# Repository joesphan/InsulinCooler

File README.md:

# Insulin Cooler

This repository is for my senior project

#### Problem Statement

There is a large population of diabetic citizens who require doses of insulin every day. Long-term portable methods of insulin storage are very expensive.

#### Methodology and Limitations

Insulin must be stored at temperatures from 36&deg;F to 46&deg;F. Using 3d printing to maximalize thermal insulation in the chassis, combined with peltier coolers, lithium-ion batteries and IOT ESP32, it should be reasonably feasible to create a cooler for under $50.

The specs I submitted for my coursework states that the cooler must have a battery life of at least 48 hours. However, I have made it a personal goal to maximize thermal efficiency to achieve two weeks or more.

Using 3d printing, I should be able to create an airgap insulation.

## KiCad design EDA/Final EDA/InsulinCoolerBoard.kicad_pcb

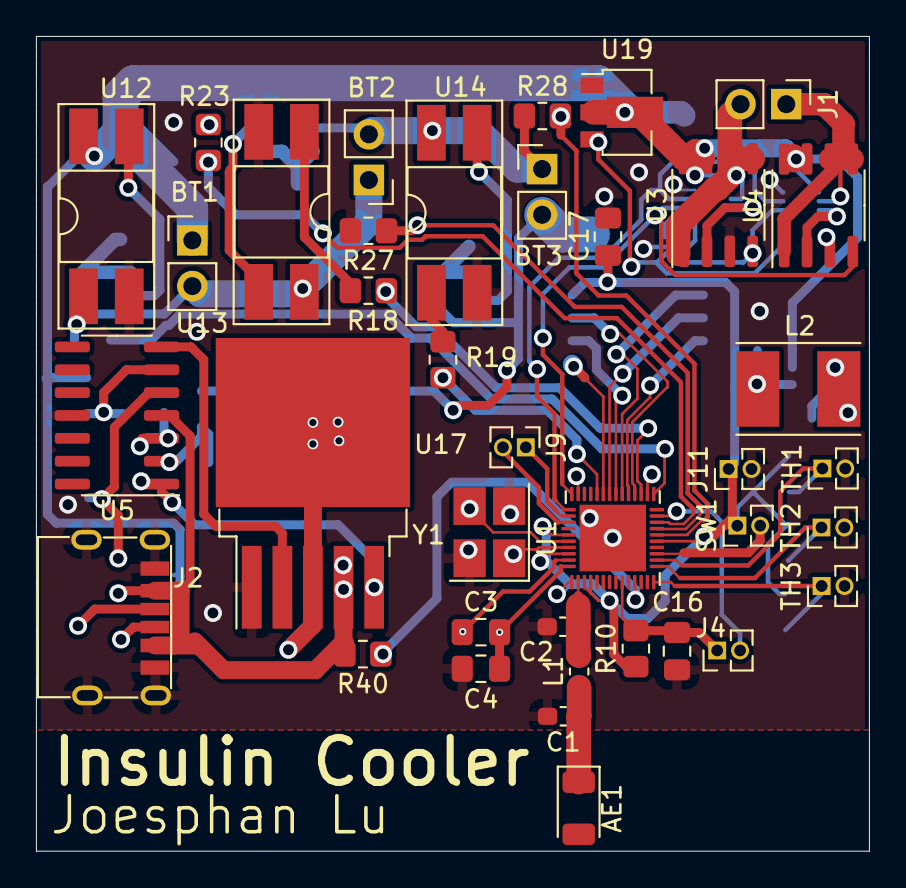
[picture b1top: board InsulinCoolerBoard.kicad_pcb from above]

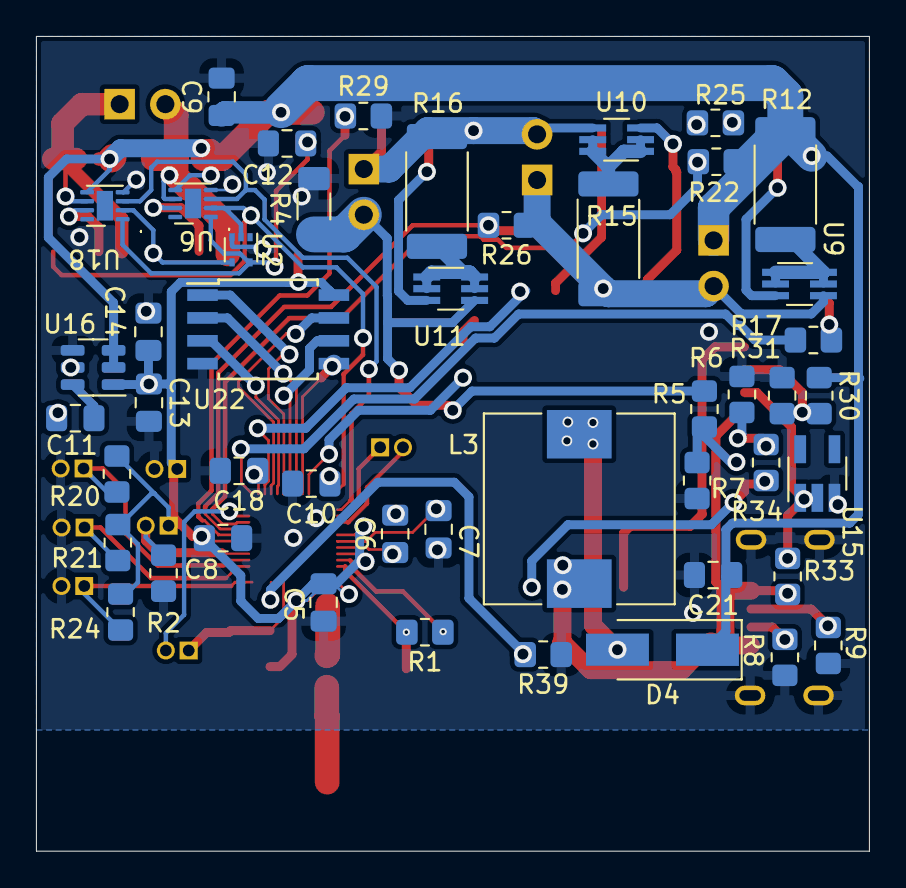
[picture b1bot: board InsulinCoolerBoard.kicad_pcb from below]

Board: 2 copper layers, 46.3 x 45.3 mm, 85 parts (47 on the bottom side), 65 nets.

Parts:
AE1: Antenna_Chip; Johanson_2450AT18x100
BT1, BT2, BT3: Battery_Cell; PinHeader_1x02_P2.54mm_Vertical
C1: 3.797pF; C_0603_1608Metric_Pad1.08x0.95mm_HandSolder
C2: 4.64pF; C_0603_1608Metric_Pad1.08x0.95mm_HandSolder
C3: 3.3nF; C_0805_2012Metric_Pad1.18x1.45mm_HandSolder
C4: 10nF; C_0805_2012Metric_Pad1.18x1.45mm_HandSolder
C5, C8, C10, C11, C16, C17, C21: 100nF; C_0805_2012Metric_Pad1.18x1.45mm_HandSolder
C6, C7: 10pF; C_0805_2012Metric_Pad1.18x1.45mm_HandSolder
C9, C12: 10uF; C_0805_2012Metric_Pad1.18x1.45mm_HandSolder
C13, C14: 22uF; C_0805_2012Metric_Pad1.18x1.45mm_HandSolder
C18: 1uF; C_0805_2012Metric_Pad1.18x1.45mm_HandSolder
D4: SS34; D_SMA_Handsoldering
J1: Peltier Connection; PinHeader_1x02_P2.54mm_Vertical
J2: USB_C_Receptacle_USB2.0; USB4125-GF-A
J4, J9, J11: PROG_PORT; PinHeader_1x02_P1.27mm_Vertical
L1: 1.807nH; L_0603_1608Metric_Pad1.05x0.95mm_HandSolder
L2: 3.3uH NRS5024T3R3NMGJ; L_Taiyo-Yuden_NR-50xx_HandSoldering
L3: 33uH; L_10.4x10.4_H4.8
R1, R10: 20k; R_0805_2012Metric_Pad1.20x1.40mm_HandSolder
R2: 10k; R_0805_2012Metric_Pad1.20x1.40mm_HandSolder
R4: .1; R_1206_3216Metric_Pad1.30x1.75mm_HandSolder
R5, R6: 1k; R_0805_2012Metric_Pad1.20x1.40mm_HandSolder
R7, R34: 12.5k; R_0805_2012Metric_Pad1.20x1.40mm_HandSolder
R8, R9: 5.1k; R_0805_2012Metric_Pad1.20x1.40mm_HandSolder
R12, R15, R16: 28.7; R_2512_6332Metric_Pad1.40x3.35mm_HandSolder
R17, R18, R19: 200; R_0805_2012Metric_Pad1.20x1.40mm_HandSolder
R20, R21, R24: 90k; R_0805_2012Metric_Pad1.20x1.40mm_HandSolder
R22, R26: 180k; R_0805_2012Metric_Pad1.20x1.40mm_HandSolder
R23: 36k; R_0805_2012Metric_Pad1.20x1.40mm_HandSolder
R25: 4.3k; R_0805_2012Metric_Pad1.20x1.40mm_HandSolder
R27: 68k; R_0805_2012Metric_Pad1.20x1.40mm_HandSolder
R28: 510k; R_0805_2012Metric_Pad1.20x1.40mm_HandSolder
R29: 620k; R_0805_2012Metric_Pad1.20x1.40mm_HandSolder
R30: 200k; R_0805_2012Metric_Pad1.20x1.40mm_HandSolder
R31: 51k; R_0805_2012Metric_Pad1.20x1.40mm_HandSolder
R33: 500; R_0805_2012Metric_Pad1.20x1.40mm_HandSolder
R39: 150k; R_0805_2012Metric_Pad1.20x1.40mm_HandSolder
R40: 100k; R_0805_2012Metric_Pad1.20x1.40mm_HandSolder
SW1: Power Switch; PinHeader_1x02_P1.27mm_Vertical
TH1, TH2, TH3: SDNT2012X103F3950FTF; PinHeader_1x02_P1.27mm_Vertical
U1: ESP32-D-WD-V3; QFN-48-1EP_5x5mm_P0.35mm_EP3.7x3.7mm
U2: NL17SZ14; SOT-553
U3, U4: DMT3020LSDQ; SO-8_3.9x4.9mm_P1.27mm
U5: LM324; SOIC-14_3.9x8.7mm_P1.27mm
U6, U18: slg55021; TDFN_8_2x2mm_EP_0.9x1.65mm
U9, U10, U11: BSD316; SOT-363_SC-70-6_Handsoldering
U12, U13, U14: PC817; DIP-4_W8.89mm_SMDSocket_LongPads
U15: AS431; SOT-23-5_HandSoldering
U16: AP63203WU; TSOT-23-6
U17: XL6009; TO-263-5_TabPin3
U19: HT75xx-1-SOT89; SOT-89-3
U22: W25Q40CL; SOIC-8W_5.3x5.3mm_P1.27mm
Y1: Crystal_GND24; Crystal_SMD_SeikoEpson_FA238-4Pin_3.2x2.5mm_HandSoldering

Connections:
+3V3: C5.1, C8.1, C13.1, C14.1, C17.1, J11.1, L2.2, R10.1, R20.1, R21.1, R24.1, SW1.1, U1.1 (VDDA), U1.3 (VDD3P3), U1.4 (VDD3P3), U1.19 (VDD3P3_RTC), U1.43 (VDDA), U1.46 (VDDA), U16.1 (FB), U22.8 (VCC)
+5V: C12.1, U2.5 (VCC), U6.1 (VCC), U18.1 (VCC), U19.3 (VOUT)
/MCU/CELL_DSCHG_1_MCU: R19.2, U1.34 (GPIO5)
/MCU/CELL_DSCHG_2_MCU: R18.2, U1.27 (GPIO17)
/MCU/CELL_DSCHG_3_MCU: R17.2, U1.25 (GPIO16)
/MCU/CELL_MEAS_1_MCU: R28.2, R29.1, U1.20 (GPIO13/MTCK)
/MCU/CELL_MEAS_2_MCU: R26.2, R27.1, U1.21 (GPIO15/MTDO)
/MCU/CELL_MEAS_3_MCU: R22.2, R23.1, U1.22 (GPIO2)
/MCU/DRIVER_DIR_MCU: U1.38 (GPIO19), U2.2 (A), U4.4 (G), U6.2 (ON)
/MCU/DRIVER_EN_MCU: U1.39 (GPIO22), U6.3 (SHDN#), U18.3 (SHDN#)
/MCU/EN: C16.1, J4.1, R10.2, U1.9 (CHIP_PU)
/MCU/IO0: J4.2, U1.23 (GPIO0)
/MCU/PWR_SW_P_MCU: R2.2, SW1.2, U1.17 (GPIO14/MTMS)
/MCU/RXD_MCU: J9.1, U1.40 (U0RXD)
/MCU/SD_CLK: U1.31 (SD_CLK), U22.6 (CLK)
/MCU/SD_CMD: U1.30 (SD_CMD), U22.1 (~CS)
/MCU/SD_DATA_0: U1.32 (SD_DATA_0), U22.2 (DO)
/MCU/SD_DATA_1: U1.33 (SD_DATA_1), U22.5 (DI)
/MCU/SD_DATA_2: U1.28 (SD_DATA_2), U22.7 (~HOLD)
/MCU/SD_DATA_3: U1.29 (SD_DATA_3), U22.3 (~WP)
/MCU/TEMP_SENSE_1: R20.2, TH1.1, U1.16 (GPIO27)
/MCU/TEMP_SENSE_2: R21.2, TH2.1, U1.15 (GPIO26)
/MCU/TEMP_SENSE_3: R24.2, TH3.1, U1.14 (GPIO25)
/MCU/TXD_MCU: J9.2, U1.41 (U0TXD)
/Peltier Driver/~DRIVER_DIR_PD: U2.4 (Y), U3.4 (G), U18.2 (ON)
GND: C1.2, C2.2, C4.2, C5.2, C6.2, C7.2, C8.2, C9.2, C10.2, C12.2, C13.2, C14.2, C16.2, C17.2, C18.2, C21.2, J2.A12 (GND), J2.B12 (GND), J2.S1 (SHIELD), J11.2, R2.1, R4.1, R6.2, R7.2, R8.2, R9.2, R25.2, R27.2, R29.2, R31.2, R39.1, TH1.2, TH2.2, TH3.2, U1.49 (GND_EP), U2.3 (GND), U3.3 (S), U4.3 (S), U5.11 (V-), U6.4 (GND), U12.2, U13.2, U14.2, U15.3, U16.4 (GND), U17.1 (GND), U18.4 (GND), U19.1 (GND), U22.4 (GND), Y1.2, Y1.4
unnamed: AE1.1 (FEED), C1.1, L1.1
unnamed: BT1.2 (-), BT2.1 (+), R15.1, R26.1, U9.4 (S), U13.4
unnamed: BT2.2 (-), BT3.1 (+), R16.1, R28.1, U10.4 (S), U14.4
unnamed: BT3.2 (-), R4.2, R5.2, U11.4 (S)
unnamed: C2.1, L1.2, U1.2 (LNA_IN)
unnamed: C3.1, R1.1, U1.47 (CAP2)
unnamed: C3.2, C4.1, R1.2, U1.48 (CAP1)
unnamed: C6.1, U1.45 (XTAL_P), Y1.1
unnamed: C7.1, U1.44 (XTAL_N), Y1.3
unnamed: C10.1, U1.37 (VDD3P3_CPU)
unnamed: C11.1, L2.1, U16.5 (SW)
unnamed: C11.2, U16.6 (BST)
unnamed: C18.1, U1.26 (VDD_SDIO)
unnamed: D4.2 (A), L3.2, U17.3 (SW)
unnamed: J1.1, U4.1 (S), U4.5 (D), U4.6 (D), U18.6 (S)
unnamed: J1.2, U3.1 (S), U3.5 (D), U3.6 (D), U6.6 (S)
unnamed: J2.A5 (CC1), R9.1
unnamed: J2.B5 (CC2), R8.1
unnamed: R5.1, R7.1, U5.2 (-)
unnamed: R12.2, U9.1 (D), U9.2 (D), U9.5 (D), U9.6 (D)
unnamed: R15.2, U10.1 (D), U10.2 (D), U10.5 (D), U10.6 (D)
unnamed: R16.2, U11.1 (D), U11.2 (D), U11.5 (D), U11.6 (D)
unnamed: R17.1, U12.1
unnamed: R18.1, U13.1
unnamed: R19.1, U14.1
unnamed: R23.2, R25.1
unnamed: R30.2, R31.1, U5.6 (-)
unnamed: R33.2, U5.5 (+), U15.1, U15.2
unnamed: R6.1, R34.1, U5.3 (+)
unnamed: R34.2, U5.1, U17.5 (FB)
unnamed: R39.2, R40.1, U1.11 (GPIO35/VDET_2)
unnamed: U3.2 (G), U6.7 (G)
unnamed: U10.3 (G), U13.3
unnamed: U11.3 (G), U14.3
unnamed: U9.3 (G), U12.3
unnamed: U5.7, U17.2 (EN)
unnamed: U4.2 (G), U18.7 (G)
PWR_UNREG: BT1.1 (+), C9.1, C21.1, D4.1 (K), R12.1, R22.1, R30.1, U3.7 (D), U3.8 (D), U4.7 (D), U4.8 (D), U6.5 (D), U12.4, U16.2 (EN), U16.3 (IN), U18.5 (D), U19.2 (VIN)
VBUS: J2.A9 (VBUS), J2.B9 (VBUS), L3.1, R33.1, R40.2, U5.4 (V+), U17.4 (VIN)

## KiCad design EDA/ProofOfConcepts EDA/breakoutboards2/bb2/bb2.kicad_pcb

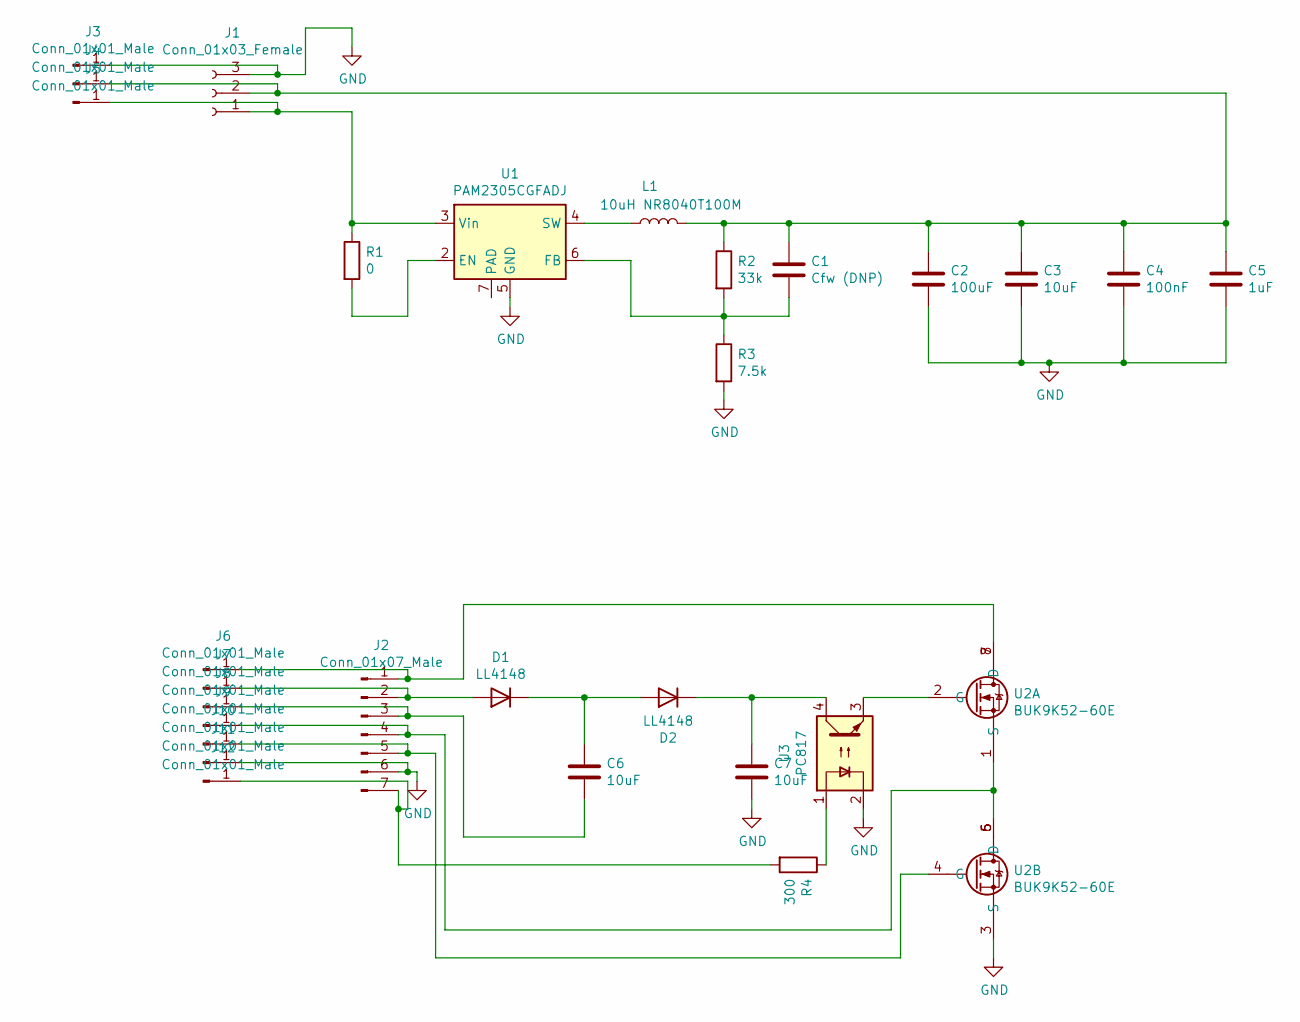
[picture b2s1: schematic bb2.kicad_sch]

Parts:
C1: Cfw (DNP); C_0805_2012Metric_Pad1.18x1.45mm_HandSolder
C2: 100uF; C_1210_3225Metric_Pad1.33x2.70mm_HandSolder
C3, C6, C7: 10uF; C_0805_2012Metric_Pad1.18x1.45mm_HandSolder
C4: 100nF; C_0805_2012Metric_Pad1.18x1.45mm_HandSolder
C5: 1uF; C_0805_2012Metric_Pad1.18x1.45mm_HandSolder
D1, D2: LL4148; D_MiniMELF
J1: Conn_01x03_Female; PinHeader_1x03_P2.54mm_Vertical
J2: Conn_01x07_Male; PinHeader_1x07_P2.54mm_Vertical
J3, J4, J5, J6, J7, J8, J9, J10, J11, J12: Conn_01x01_Male; GatorTestpoint
L1: 10uH NR8040T100M; L_Taiyo-Yuden_NR-80xx_HandSoldering
R1: 0; R_0805_2012Metric_Pad1.20x1.40mm_HandSolder
R2: 33k; R_0805_2012Metric_Pad1.20x1.40mm_HandSolder
R3: 7.5k; R_0805_2012Metric_Pad1.20x1.40mm_HandSolder
R4: 300; R_0805_2012Metric_Pad1.20x1.40mm_HandSolder
U1: PAM2305CGFADJ; DFN-6-1EP_2x2mm_P0.65mm_EP1x1.6mm
U2: BUK9K52-60E; LFPAK56D
U3: PC817; SOP-4_3.8x4.1mm_P2.54mm

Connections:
GND: C2.2, C3.2, C4.2, C5.2, C7.2, J1.3, J2.6, J3.1, J11.1, R3.2, U1.5 (GND), U2.3 (S), U3.2
unnamed: C1.1, C2.1, C3.1, C4.1, C5.1, J1.2, J4.1, L1.2, R2.1
unnamed: C1.2, R2.2, R3.1, U1.6 (FB)
unnamed: C6.1, D1.1 (K), D2.2 (A)
unnamed: C6.2, J2.3, J8.1
unnamed: C7.1, D2.1 (K), U3.4
unnamed: D1.2 (A), J2.2, J7.1
unnamed: J1.1, J5.1, R1.1, U1.3 (Vin)
unnamed: J2.1, J6.1, U2.7 (D), U2.8 (D)
unnamed: J2.4, J9.1, U2.1 (S), U2.5 (D), U2.6 (D)
unnamed: J2.5, J10.1, U2.4 (G)
unnamed: J2.7, J12.1, R4.2
unnamed: L1.1, U1.4 (SW)
unnamed: R1.2, U1.2 (EN)
unnamed: R4.1, U3.1
unnamed: U2.2 (G), U3.3

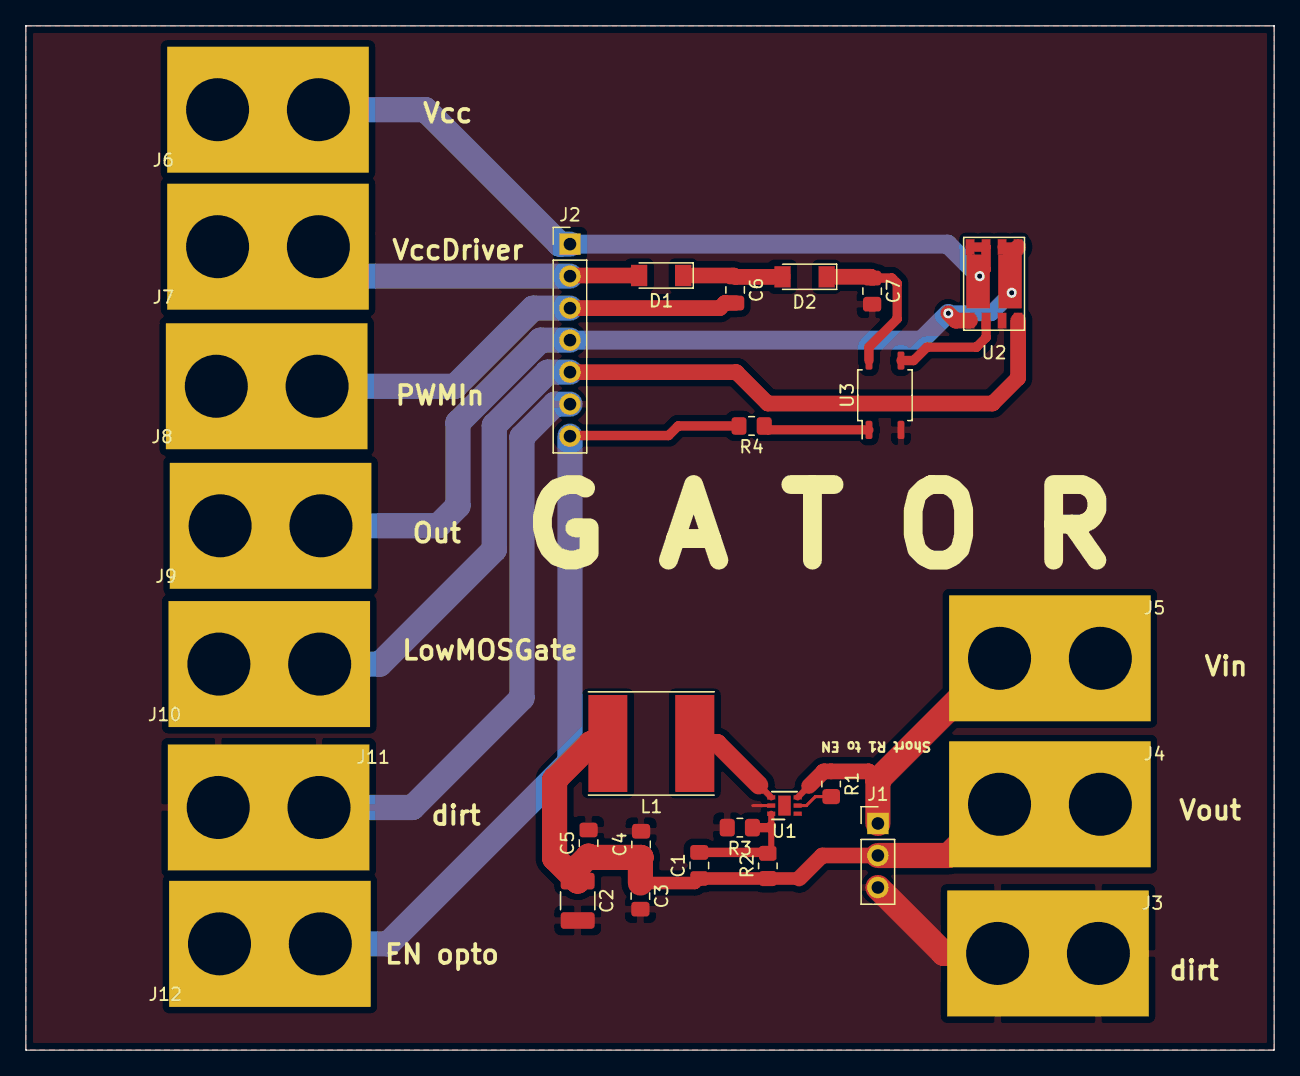
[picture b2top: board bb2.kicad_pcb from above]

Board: 2 copper layers, 99.1 x 81.3 mm, 29 parts (0 on the bottom side), 16 nets.

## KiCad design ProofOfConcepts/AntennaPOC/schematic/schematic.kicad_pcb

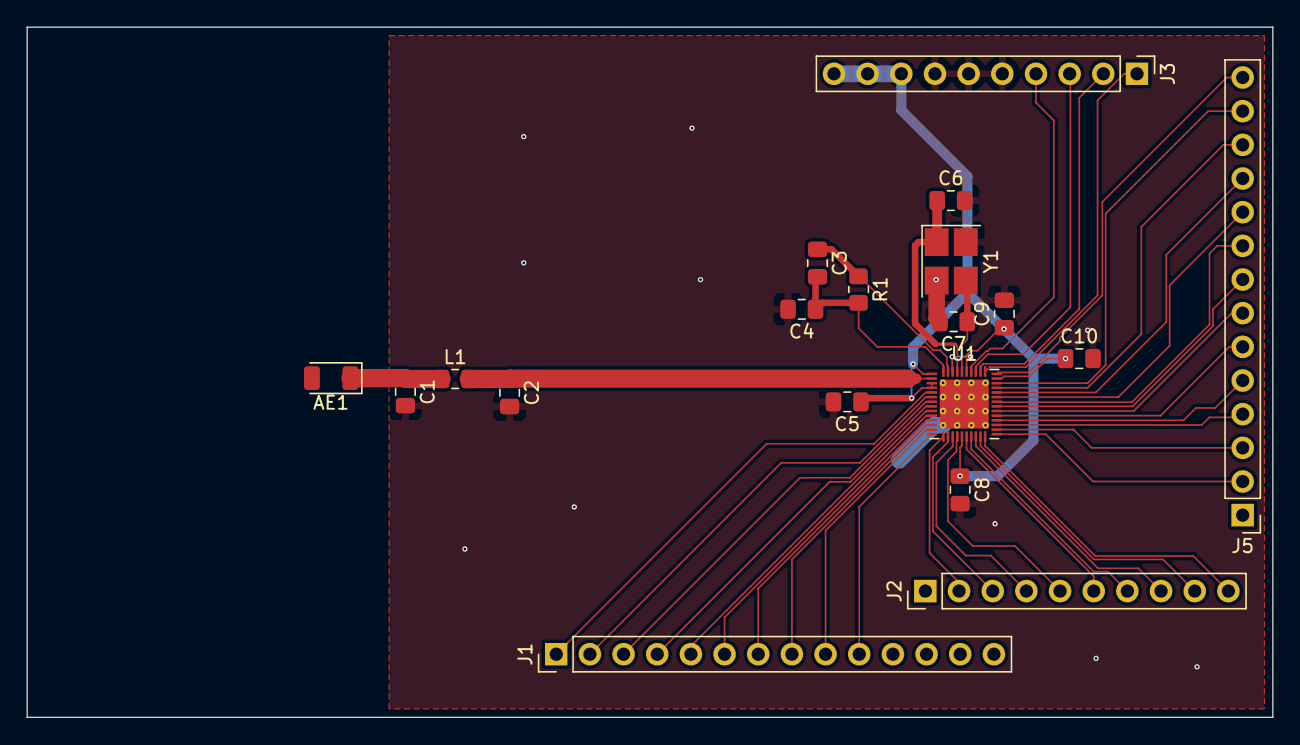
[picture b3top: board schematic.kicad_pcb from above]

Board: 2 copper layers, 94.0 x 52.1 mm, 19 parts (0 on the bottom side), 44 nets.

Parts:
AE1: Antenna_Chip; Johanson_2450AT18x100
C1: 3.797pF; C_0805_2012Metric_Pad1.18x1.45mm_HandSolder
C2: 4.64pF; C_0805_2012Metric_Pad1.18x1.45mm_HandSolder
C3: 3.3nF; C_0805_2012Metric_Pad1.18x1.45mm_HandSolder
C4: 10nF; C_0805_2012Metric_Pad1.18x1.45mm_HandSolder
C5, C8, C9, C10: 100nF; C_0805_2012Metric_Pad1.18x1.45mm_HandSolder
C6, C7: 10pF; C_0805_2012Metric_Pad1.18x1.45mm_HandSolder
J1, J5: Conn_01x14_Male; PinHeader_1x14_P2.54mm_Vertical
J2, J3: Conn_01x10_Male; PinHeader_1x10_P2.54mm_Vertical
L1: 1.807nH; L_0805_2012Metric_Pad1.15x1.40mm_HandSolder
R1: 20k; R_0805_2012Metric_Pad1.20x1.40mm_HandSolder
U1: ESP32-D-WD-V3; QFN-48-1EP_5x5mm_P0.35mm_EP3.7x3.7mm_ThermalVias
Y1: Crystal_GND24; Crystal_SMD_SeikoEpson_FA238-4Pin_3.2x2.5mm_HandSoldering

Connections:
+3V3: C5.1, C8.1, C9.1, C10.1, J3.8, J3.9, J3.10, U1.1, U1.3, U1.4, U1.19, U1.37, U1.43, U1.46
GND: C1.2, C2.2, C4.2, C5.2, C6.2, C7.2, C8.2, C9.2, C10.2, J3.5, J3.6, J3.7, U1.49, Y1.2, Y1.4
unnamed: AE1.1, C1.1, L1.1
unnamed: C2.1, L1.2, U1.2
unnamed: C3.1, R1.1, U1.47
unnamed: C3.2, C4.1, R1.2, U1.48
unnamed: C6.1, U1.45, Y1.1
unnamed: C7.1, U1.44, Y1.3
unnamed: J1.1, U1.5
unnamed: J1.2, U1.6
unnamed: J1.3, U1.7
unnamed: J1.4, U1.8
unnamed: J1.5, U1.9
unnamed: J1.6, U1.10
unnamed: J1.7, U1.11
unnamed: J1.8, U1.12
unnamed: J1.9, U1.13
unnamed: J1.10, U1.14
unnamed: J2.2, U1.15
unnamed: J2.3, U1.16
unnamed: J2.4, U1.17
unnamed: J2.5, U1.18
unnamed: J2.6, U1.20
unnamed: J2.7, U1.21
unnamed: J2.8, U1.22
unnamed: J2.9, U1.23
unnamed: J2.10, U1.24
unnamed: J3.1, U1.39
unnamed: J3.2, U1.40
unnamed: J3.3, U1.41
unnamed: J3.4, U1.42
unnamed: J5.2, U1.25
unnamed: J5.3, U1.26
unnamed: J5.4, U1.27
unnamed: J5.5, U1.28
unnamed: J5.6, U1.29
unnamed: J5.7, U1.30
unnamed: J5.8, U1.31
unnamed: J5.9, U1.32
unnamed: J5.10, U1.33
unnamed: J5.11, U1.34
unnamed: J5.12, U1.35
unnamed: J5.13, U1.36
unnamed: J5.14, U1.38

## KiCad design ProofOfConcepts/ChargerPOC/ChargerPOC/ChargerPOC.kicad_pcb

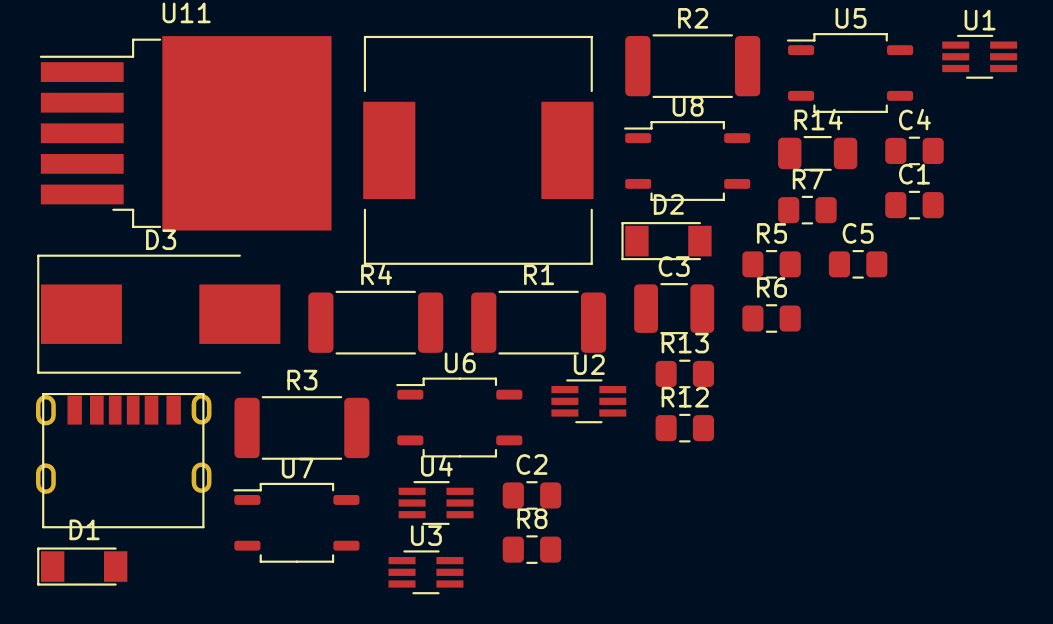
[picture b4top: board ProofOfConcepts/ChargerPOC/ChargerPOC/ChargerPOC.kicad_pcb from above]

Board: 2 copper layers, 30 parts (0 on the bottom side), 24 nets, no tracks yet.

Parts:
C1, C2: 10uF; C_0805_2012Metric_Pad1.18x1.45mm_HandSolder
C3: 100uF; C_1210_3225Metric_Pad1.33x2.70mm_HandSolder
C4: 1uF; C_0805_2012Metric_Pad1.18x1.45mm_HandSolder
C5: 100nF; C_0805_2012Metric_Pad1.18x1.45mm_HandSolder
D1, D2: LL4148; D_MiniMELF
D3: SS34; D_SMC_Handsoldering
J4: USB_C_Receptacle_USB2.0; USB4125-GF-A
L1: 33uH; L_12x12mm_H4.5mm
R1, R2, R3, R4: 28.7; R_2512_6332Metric_Pad1.40x3.35mm_HandSolder
R5, R6, R7, R8: 200; C_0805_2012Metric_Pad1.18x1.45mm_HandSolder
R12, R13: 5.1k; C_0805_2012Metric_Pad1.18x1.45mm_HandSolder
R14: .1; R_1206_3216Metric_Pad1.30x1.75mm_HandSolder
U1, U2, U3, U4: BSD316; SOT-363_SC-70-6_Handsoldering
U5, U6, U7, U8: PC817; SOP-4_3.8x4.1mm_P2.54mm
U11: XL6009; TO-263-5_TabPin3

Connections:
+BATT: C3.1, C4.1, C5.1, D1.2 (A), D3.1 (K), R1.1
GND: C2.2, C3.2, C4.2, C5.2, J4.A12 (GND), J4.B12 (GND), J4.S1 (SHIELD), R12.2, R13.2, R14.2, U4.4 (S), U5.2, U6.2, U7.2, U8.2
unnamed: R2.1, U1.4 (S)
unnamed: R3.1, U2.4 (S)
unnamed: R4.1, U3.4 (S)
unnamed: C1.1, D1.1 (K), D2.2 (A)
unnamed: D3.2 (A), L1.2, U11.3 (SW)
unnamed: J4.A5 (CC1), R13.1
unnamed: J4.B5 (CC2), R12.1
unnamed: R1.2, U1.1 (D), U1.2 (D), U1.5 (D), U1.6 (D)
unnamed: R2.2, U2.1 (D), U2.2 (D), U2.5 (D), U2.6 (D)
unnamed: R3.2, U3.1 (D), U3.2 (D), U3.5 (D), U3.6 (D)
unnamed: R4.2, U4.1 (D), U4.2 (D), U4.5 (D), U4.6 (D)
unnamed: R5.1, U5.1
unnamed: R6.1, U6.1
unnamed: R7.1, U7.1
unnamed: R8.1, U8.1
unnamed: R14.1, U11.1 (GND)
unnamed: U1.3 (G), U5.3
unnamed: U2.3 (G), U6.3
unnamed: U3.3 (G), U7.3
unnamed: U4.3 (G), U8.3
VBUS: J4.A9 (VBUS), J4.B9 (VBUS), L1.1, U11.4 (VIN)
Vdrive: C2.1, D2.1 (K), U5.4, U6.4, U7.4, U8.4

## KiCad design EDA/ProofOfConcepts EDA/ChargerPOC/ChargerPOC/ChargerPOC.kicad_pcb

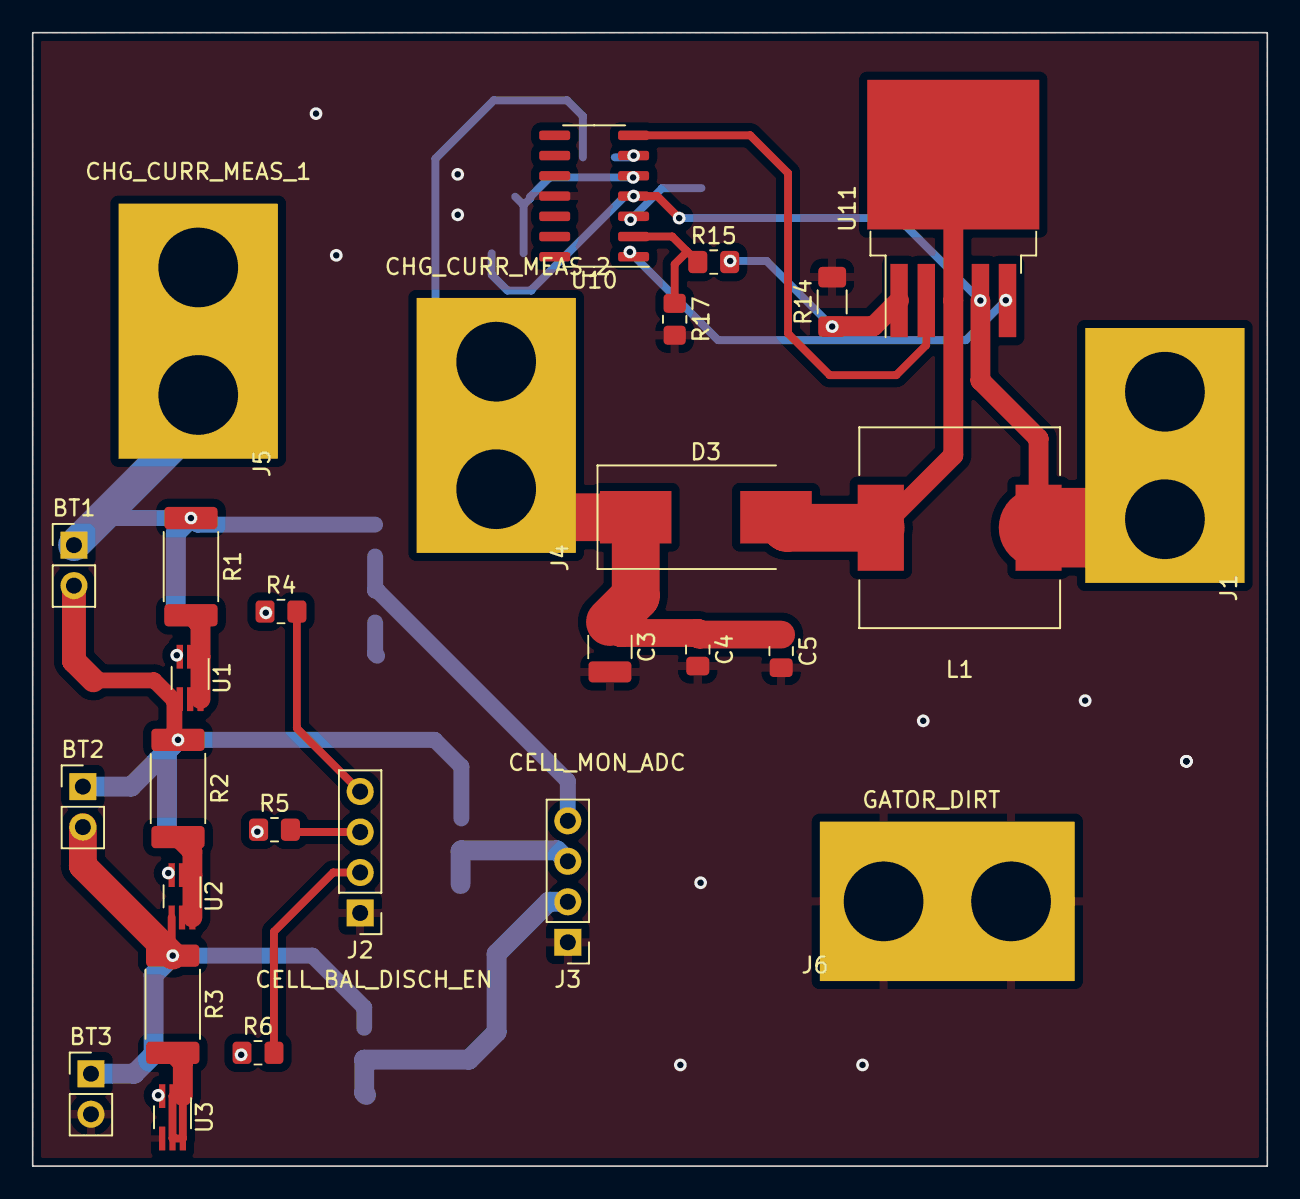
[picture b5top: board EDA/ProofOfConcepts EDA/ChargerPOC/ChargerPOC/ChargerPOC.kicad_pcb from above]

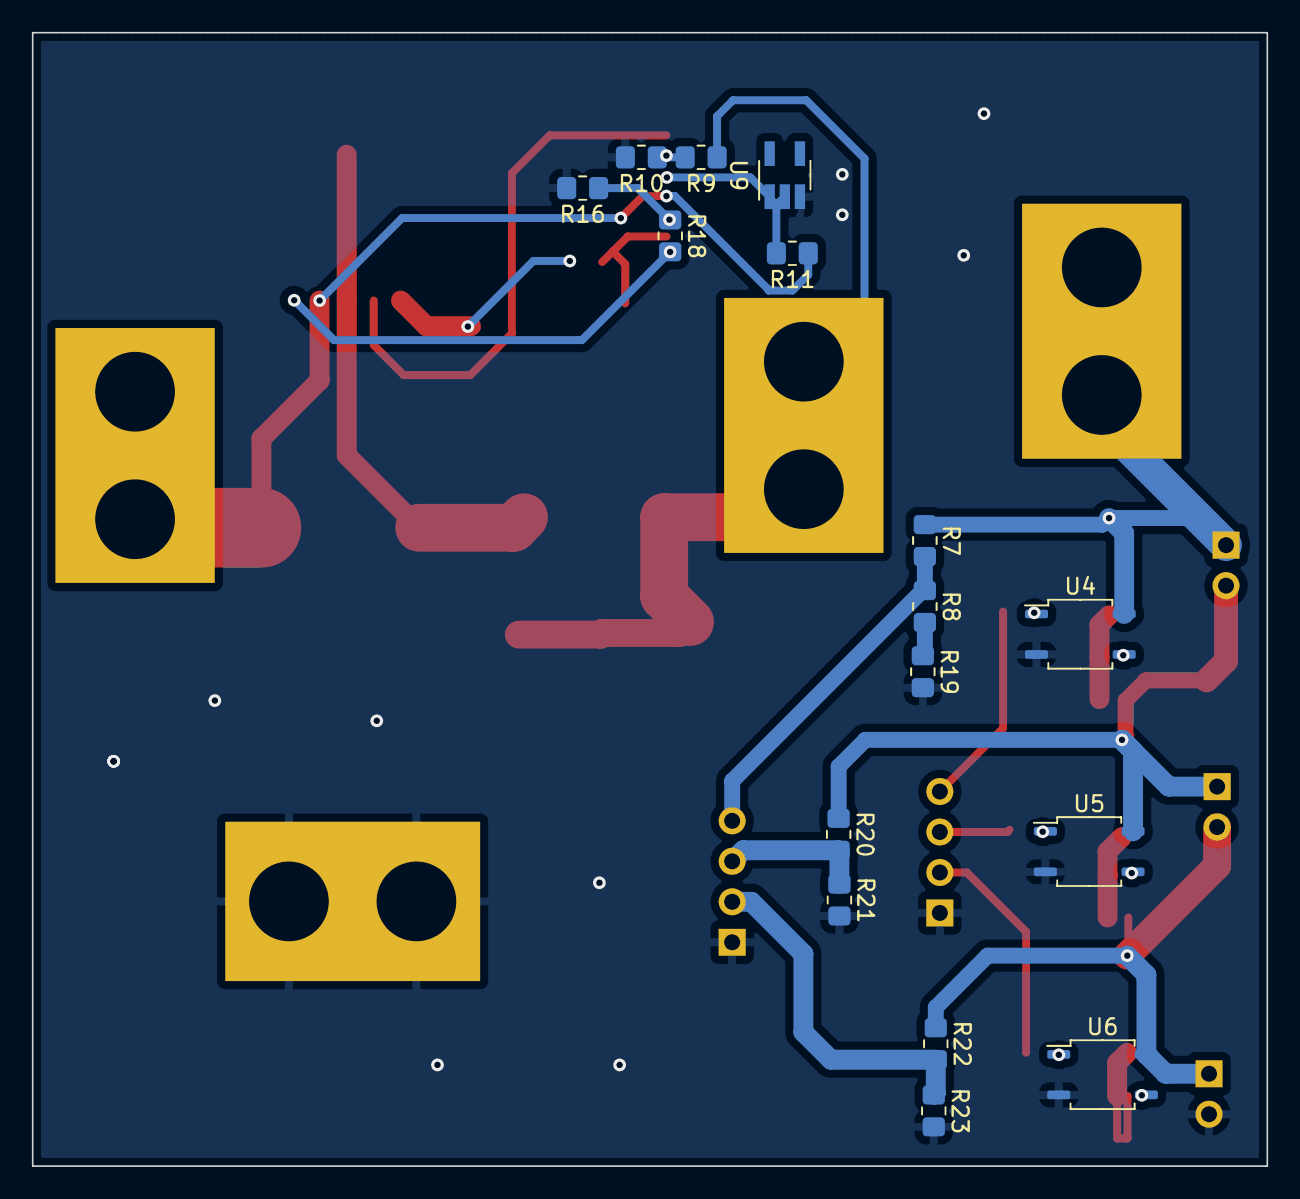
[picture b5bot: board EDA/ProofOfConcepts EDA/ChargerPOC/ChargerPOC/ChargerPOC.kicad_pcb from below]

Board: 2 copper layers, 77.5 x 71.1 mm, 44 parts (16 on the bottom side), 30 nets.

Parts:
BT1, BT2, BT3: Battery_Cell; PinHeader_1x02_P2.54mm_Vertical
C3: 100uF; C_1210_3225Metric_Pad1.33x2.70mm_HandSolder
C4: 1uF; C_0805_2012Metric_Pad1.18x1.45mm_HandSolder
C5: 100nF; C_0805_2012Metric_Pad1.18x1.45mm_HandSolder
D3: SS34; D_SMC_Handsoldering
J1: VIN; GatorTestpoint
J2: CELL_BAL_DISCH_EN; PinHeader_1x04_P2.54mm_Vertical
J3: CELL_MON_ADC; PinHeader_1x04_P2.54mm_Vertical
J4: CHG_CURR_MEAS_2; GatorTestpoint
J5: CHG_CURR_MEAS_1; GatorTestpoint
J6: GATOR_DIRT; GatorTestpoint
L1: 33uH; L_12x12mm_H4.5mm
R1, R2, R3: 28.7; R_2512_6332Metric_Pad1.40x3.35mm_HandSolder
R4, R5, R6: 200; R_0805_2012Metric_Pad1.20x1.40mm_HandSolder
R7, R9: 100k; R_0805_2012Metric_Pad1.20x1.40mm_HandSolder
R8: 22k; R_0805_2012Metric_Pad1.20x1.40mm_HandSolder
R10: 18k; R_0805_2012Metric_Pad1.20x1.40mm_HandSolder
R11: 500; R_0805_2012Metric_Pad1.20x1.40mm_HandSolder
R14: .1; R_1206_3216Metric_Pad1.30x1.75mm_HandSolder
R15, R16: 1k; R_0805_2012Metric_Pad1.20x1.40mm_HandSolder
R17, R18: 12.5k; R_0805_2012Metric_Pad1.20x1.40mm_HandSolder
R19: 390; R_0805_2012Metric_Pad1.20x1.40mm_HandSolder
R20: 180k; R_0805_2012Metric_Pad1.20x1.40mm_HandSolder
R21, R23: 68k; R_0805_2012Metric_Pad1.20x1.40mm_HandSolder
R22: 56k; R_0805_2012Metric_Pad1.20x1.40mm_HandSolder
U1, U2, U3: BSD316; SOT-363_SC-70-6_Handsoldering
U4, U5, U6: PC817; SOP-4_3.8x4.1mm_P2.54mm
U9: AS431; SOT-23-5_HandSoldering
U10: LM324; SOIC-14_3.9x8.7mm_P1.27mm
U11: XL6009; TO-263-5_TabPin3

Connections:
+BATT: C3.1, C4.1, C5.1, D3.1 (K), J4.1, R9.1
GND: BT3.2 (-), C3.2, C4.2, C5.2, J2.1, J3.1, J6.1, R10.2, R14.2, R16.2, R17.2, R19.2, R21.2, R23.2, U3.4 (S), U4.2, U5.2, U6.2, U9.3, U10.11 (V-)
unnamed: BT1.1 (+), J5.1, R1.1, R7.1, U4.4
unnamed: BT1.2 (-), BT2.1 (+), R2.1, R20.1, U1.4 (S), U5.4
unnamed: BT2.2 (-), BT3.1 (+), R3.1, R22.1, U2.4 (S), U6.4
unnamed: D3.2 (A), L1.2, U11.3 (SW)
unnamed: J2.2, R6.2
unnamed: J2.3, R5.2
unnamed: J2.4, R4.2
unnamed: J3.2, R22.2, R23.1
unnamed: J3.3, R20.2, R21.1
unnamed: J3.4, R7.2, R8.1
unnamed: R1.2, U1.1 (D), U1.2 (D), U1.5 (D), U1.6 (D)
unnamed: R2.2, U2.1 (D), U2.2 (D), U2.5 (D), U2.6 (D)
unnamed: R3.2, U3.1 (D), U3.2 (D), U3.5 (D), U3.6 (D)
unnamed: R4.1, U4.1
unnamed: R5.1, U5.1
unnamed: R6.1, U6.1
unnamed: R9.2, R10.1, U10.6 (-)
unnamed: R11.2, U9.1, U9.2, U10.5 (+)
unnamed: R14.1, R15.2, U11.1 (GND)
unnamed: R15.1, R17.1, U10.2 (-)
unnamed: R16.1, R18.1, U10.3 (+)
unnamed: R18.2, U10.1, U11.5 (FB)
unnamed: R8.2, R19.1
unnamed: U1.3 (G), U4.3
unnamed: U2.3 (G), U5.3
unnamed: U3.3 (G), U6.3
unnamed: U10.7, U11.2 (EN)
VBUS: J1.1, L1.1, R11.1, U10.4 (V+), U11.4 (VIN)

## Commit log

2022-01-26 e
    e
2022-01-31 schematic done
2022-02-02 nightly
2022-02-03 pdfs
2022-02-03 blob
2022-02-15 fixed vias
2022-02-19 gerber push
2022-03-04 updated resistor dividers for more friendly values
2022-03-06 replacing buck converter with higher efficiency one
2022-03-08 breakout board for v2 buck and nmos driver
2022-03-19 final winter qtr push
2022-03-31 reorg + course docs
2022-04-11 beta boards routed
2022-04-22 prelim ble working
2022-06-02 code done ish
2022-06-06 all code done
2022-06-06 release apk
